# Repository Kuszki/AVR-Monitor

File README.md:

# AVR-Monitor

Zbiór programów i bibliotek oraz projekt urządzenia elektronicznego do badania analogowych sygnałów wolnozmiennych i sterowania urządzeń sygnałami cyfrowymi.

## Programy

### Interfejs

AVR-Interface umożliwia obsługę urządzenia przy pomocy graficznego interfejsu użytkownika. Program pozwala na monitorowanie przebiegów w czasie rzeczywistym i archiwizowanie danych. Ponadto program oferuje możliwość konfiguracji i programowania urządzenia AVR-Monitor.

### Terminal

AVR-Terminal umożliwia komunikacje z urządzeniem AVR-Monitor przy użyciu klasycznego terminalu. Jest to opcja minimalistyczna pozwalająca na zaprogramowanie i konfiguracje urządzenia oraz pozwalająca przetestować większość jego funkcji.

### Biblioteka "Bindings"

AVR-Bindings pozwala na użycie klasy ułatwiającej komunikacje z urządzeniem i nadzoruje jego pracę po podłączeniu.

### Program kontrolera

Stanowi wsad do procesora AVR użytego w projekci układu i płytki PCB.

## Urządzenia

Projekt zawiera urządzenie mikroprocesorowe oparte o mikrokontroler AVR. Na kompletne urządzenie składają się 3 schematy elektryczne - płyty głównej, front-panelu oraz płyty wierzchniej.

## Zależności

- środowisko Qt
- biblioteka KLLibs
- biblioteka QCustomPlot
- biblioteka boost

## Licencja

AVR-Monitor - Zbiór programów i bibliotek oraz projekt urządzenia elektronicznego do badania analogowych sygnałów wolnozmiennych i sterowania urządzeń sygnałami cyfrowymi. Copyright (C) 2015 Łukasz "Kuszki" Dróżdż.

Niniejszy program jest wolnym oprogramowaniem – możesz go rozpowszechniać dalej i/lub modyfikować na warunkach Powszechnej Licencji Publicznej GNU wydanej przez Fundację Wolnego Oprogramowania, według wersji 3 tej Licencji lub dowolnej z późniejszych wersji.

Niniejszy program rozpowszechniany jest z nadzieją, iż będzie on użyteczny – jednak BEZ ŻADNEJ GWARANCJI, nawet domyślnej gwarancji PRZYDATNOŚCI HANDLOWEJ albo PRZYDATNOŚCI DO OKREŚLONYCH ZASTOSOWAŃ. Bliższe informacje na ten temat można uzyskać z Powszechnej Licencji Publicznej GNU.

Kopia Powszechnej Licencji Publicznej GNU powinna zostać ci dostarczona razem z tym programem. Jeżeli nie została dostarczona, odwiedź http://www.gnu.org/licenses/.

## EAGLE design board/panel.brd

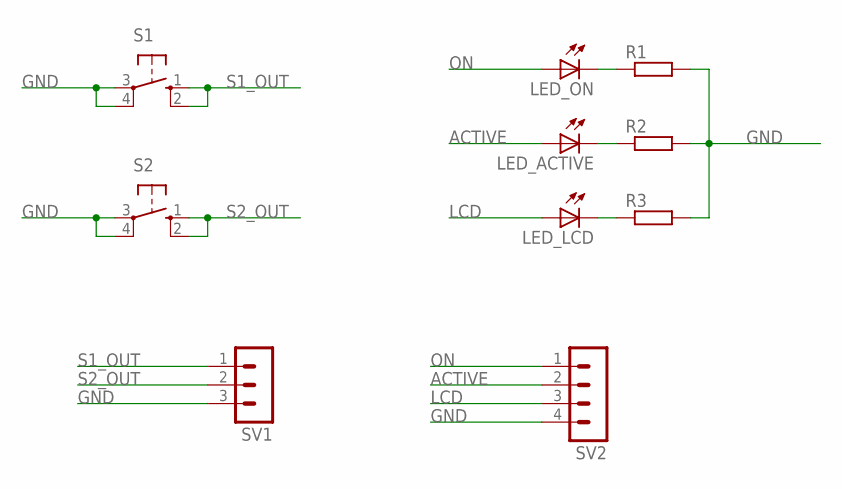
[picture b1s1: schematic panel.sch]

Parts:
LED_ACTIVE: LED_ELD260; LED_LD260
LED_LCD: LED_ELD260; LED_LD260
LED_ON: LED_ELD260; LED_LD260
R1, R2, R3: R-EU_R1206; R1206
S1, S2: 10-XX; B3F-10XX
SV1: MA03-1
SV2: MA04-1

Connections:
ACTIVE: LED_ACTIVE.A, SV2.2
GND: R1.2, R2.2, R3.2, S1.3, S1.4 (P1), S2.3, S2.4 (P1), SV1.3, SV2.4
LCD: LED_LCD.A, SV2.3
unnamed: LED_LCD.K (C), R3.1
unnamed: LED_ACTIVE.K (C), R2.1
unnamed: LED_ON.K (C), R1.1
ON: LED_ON.A, SV2.1
S1_OUT: S1.1 (S), S1.2 (S1), SV1.1
S2_OUT: S2.1 (S), S2.2 (S1), SV1.2

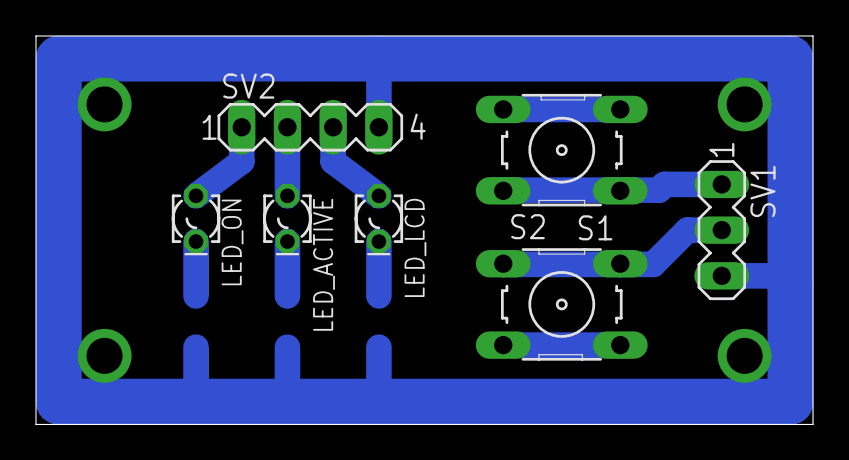
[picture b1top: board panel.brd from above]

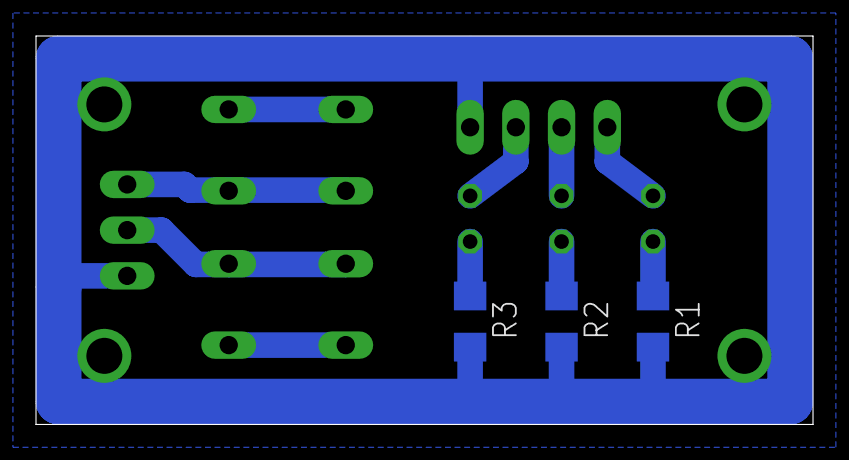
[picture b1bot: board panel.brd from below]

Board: 2 copper layers, 43.2 x 21.6 mm, 10 parts (3 on the bottom side), 9 nets.

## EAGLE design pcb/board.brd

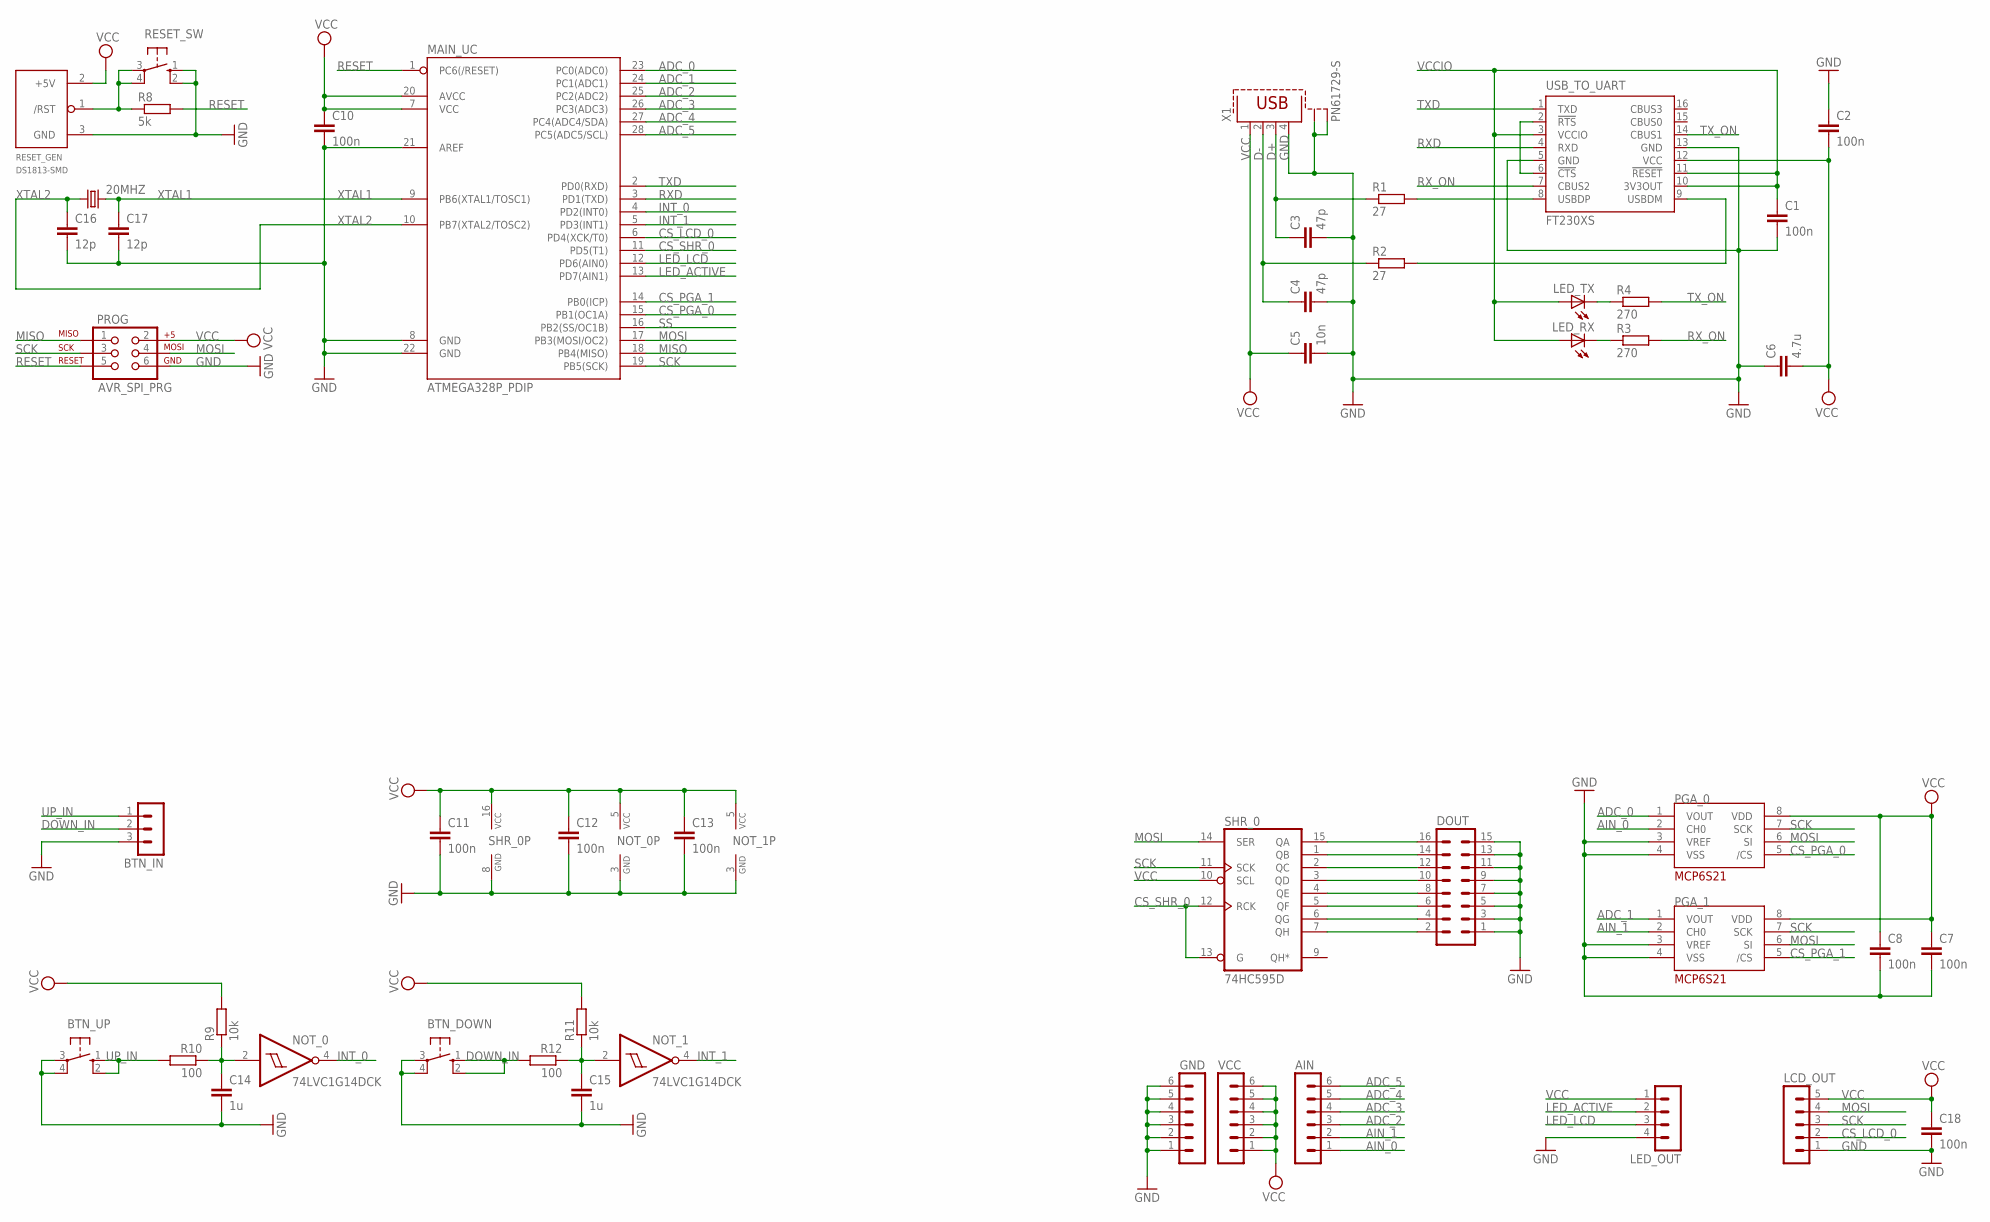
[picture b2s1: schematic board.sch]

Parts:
20MHZ: CRYSTALHC49S; HC49/S
AIN: MA06-1
BTN_DOWN: 10-XX; B3F-10XX
BTN_IN: MA03-1
BTN_UP: 10-XX; B3F-10XX
C1, C2, C7, C8, C10, C11, C12, C13, C18: 100n; C1206
C3, C4: 47p; C1206
C5: 10n; C1206
C6: 4.7u; C025-025X050
C14, C15: 1u; C025-024X044
C16, C17: 12p; C1206
DOUT: MA08-2
GND: MA06-1
LCD_OUT: MA05-1
LED_OUT: MA04-1
LED_RX: LEDLD260; LD260
LED_TX: LEDLD260; LD260
MAIN_UC: ATMEGA328P_PDIP; DIL28-3
NOT_0, NOT_1: 74LVC1G14DCK; SC70-5
PGA_0, PGA_1: MCP6S21I/SN; SO-08
PROG: AVR_SPI_PRG; 2X3
R1, R2: 27; R1206
R3, R4: 270; R1206
R8: 5k; R1206
R9, R11: 10k; R1206
R10, R12: 100; R1206
RESET_GEN: DS1813-SMD; SOT-23
RESET_SW: 10-XX; B3F-10XX
SHR_0: 74HC595D; SO16
USB_TO_UART: FT230XS; SSOP16
VCC: MA06-1
X1: PN61729-S

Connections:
ADC_0: MAIN_UC.23 (PC0(ADC0)), PGA_0.1 (VOUT)
ADC_1: MAIN_UC.24 (PC1(ADC1)), PGA_1.1 (VOUT)
ADC_2: AIN.3, MAIN_UC.25 (PC2(ADC2))
ADC_3: AIN.4, MAIN_UC.26 (PC3(ADC3))
ADC_4: AIN.5, MAIN_UC.27 (PC4(ADC4/SDA))
ADC_5: AIN.6, MAIN_UC.28 (PC5(ADC5/SCL))
AIN_0: AIN.1, PGA_0.2 (CH0)
AIN_1: AIN.2, PGA_1.2 (CH0)
CS_LCD_0: LCD_OUT.2, MAIN_UC.6 (PD4(XCK/T0))
CS_PGA_0: MAIN_UC.15 (PB1(OC1A)), PGA_0.5 (/CS)
CS_PGA_1: MAIN_UC.14 (PB0(ICP)), PGA_1.5 (/CS)
CS_SHR_0: MAIN_UC.11 (PD5(T1)), SHR_0.12 (RCK), SHR_0.13 (G)
D+: C3.1, R1.1, X1.3
D-: C4.1, R2.1, X1.2
DOWN_IN: BTN_DOWN.1 (S), BTN_DOWN.2 (S1), BTN_IN.2, R12.2
INT_0: MAIN_UC.4 (PD2(INT0)), NOT_0.4 (O)
INT_1: MAIN_UC.5 (PD3(INT1)), NOT_1.4 (O)
LED_ACTIVE: LED_OUT.2, MAIN_UC.13 (PD7(AIN1))
LED_LCD: LED_OUT.3, MAIN_UC.12 (PD6(AIN0))
MISO: MAIN_UC.18 (PB4(MISO)), PROG.1
MOSI: LCD_OUT.4, MAIN_UC.17 (PB3(MOSI/OC2)), PGA_0.6 (SI), PGA_1.6 (SI), PROG.4, SHR_0.14 (SER)
unnamed: LED_TX.K (C), R4.1
unnamed: R2.2, USB_TO_UART.9 (USBDM)
unnamed: LED_RX.K (C), R3.1
unnamed: DOUT.16, SHR_0.15 (QA)
unnamed: USB_TO_UART.2 (!RTS), USB_TO_UART.6 (!CTS)
unnamed: R1.2, USB_TO_UART.8 (USBDP)
unnamed: DOUT.14, SHR_0.1 (QB)
unnamed: DOUT.12, SHR_0.2 (QC)
unnamed: DOUT.10, SHR_0.3 (QD)
unnamed: DOUT.8, SHR_0.4 (QE)
unnamed: DOUT.6, SHR_0.5 (QF)
unnamed: DOUT.4, SHR_0.6 (QG)
unnamed: DOUT.2, SHR_0.7 (QH)
unnamed: R8.1, RESET_GEN.1 (/RST), RESET_SW.3, RESET_SW.4 (P1)
unnamed: C14.1, NOT_0.2 (I), R9.1, R10.1
unnamed: C15.1, NOT_1.2 (I), R11.1, R12.1
RESET: MAIN_UC.1 (PC6(/RESET)), PROG.5, R8.2
RXD: MAIN_UC.3 (PD1(TXD)), USB_TO_UART.4 (RXD)
RX_ON: R3.2, USB_TO_UART.7 (CBUS2)
SCK: LCD_OUT.3, MAIN_UC.19 (PB5(SCK)), PGA_0.7 (SCK), PGA_1.7 (SCK), PROG.3, SHR_0.11 (SCK)
SS: MAIN_UC.16 (PB2(SS/OC1B))
TXD: MAIN_UC.2 (PD0(RXD)), USB_TO_UART.1 (TXD)
TX_ON: R4.2, USB_TO_UART.14 (CBUS1)
UP_IN: BTN_IN.1, BTN_UP.1 (S), BTN_UP.2 (S1), R10.2
VCC: C2.2, C5.1, C6.2, C7.1, C8.1, C10.1, C11.1, C12.1, C13.1, C18.1, LCD_OUT.5, LED_OUT.1, MAIN_UC.7 (VCC), MAIN_UC.20 (AVCC), NOT_0.5 (VCC), NOT_1.5 (VCC), PGA_0.8 (VDD), PGA_1.8 (VDD), PROG.2, R9.2, R11.2, RESET_GEN.2 (+5V), SHR_0.10 (SCL), SHR_0.16 (VCC), USB_TO_UART.12 (VCC), VCC.1, VCC.2, VCC.3, VCC.4, VCC.5, VCC.6, X1.1
VCCIO: C1.1, LED_RX.A, LED_TX.A, USB_TO_UART.3 (VCCIO), USB_TO_UART.10 (3V3OUT), USB_TO_UART.11 (!RESET)
XTAL1: 20MHZ.2, C17.1, MAIN_UC.9 (PB6(XTAL1/TOSC1))
XTAL2: 20MHZ.1, C16.1, MAIN_UC.10 (PB7(XTAL2/TOSC2))

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
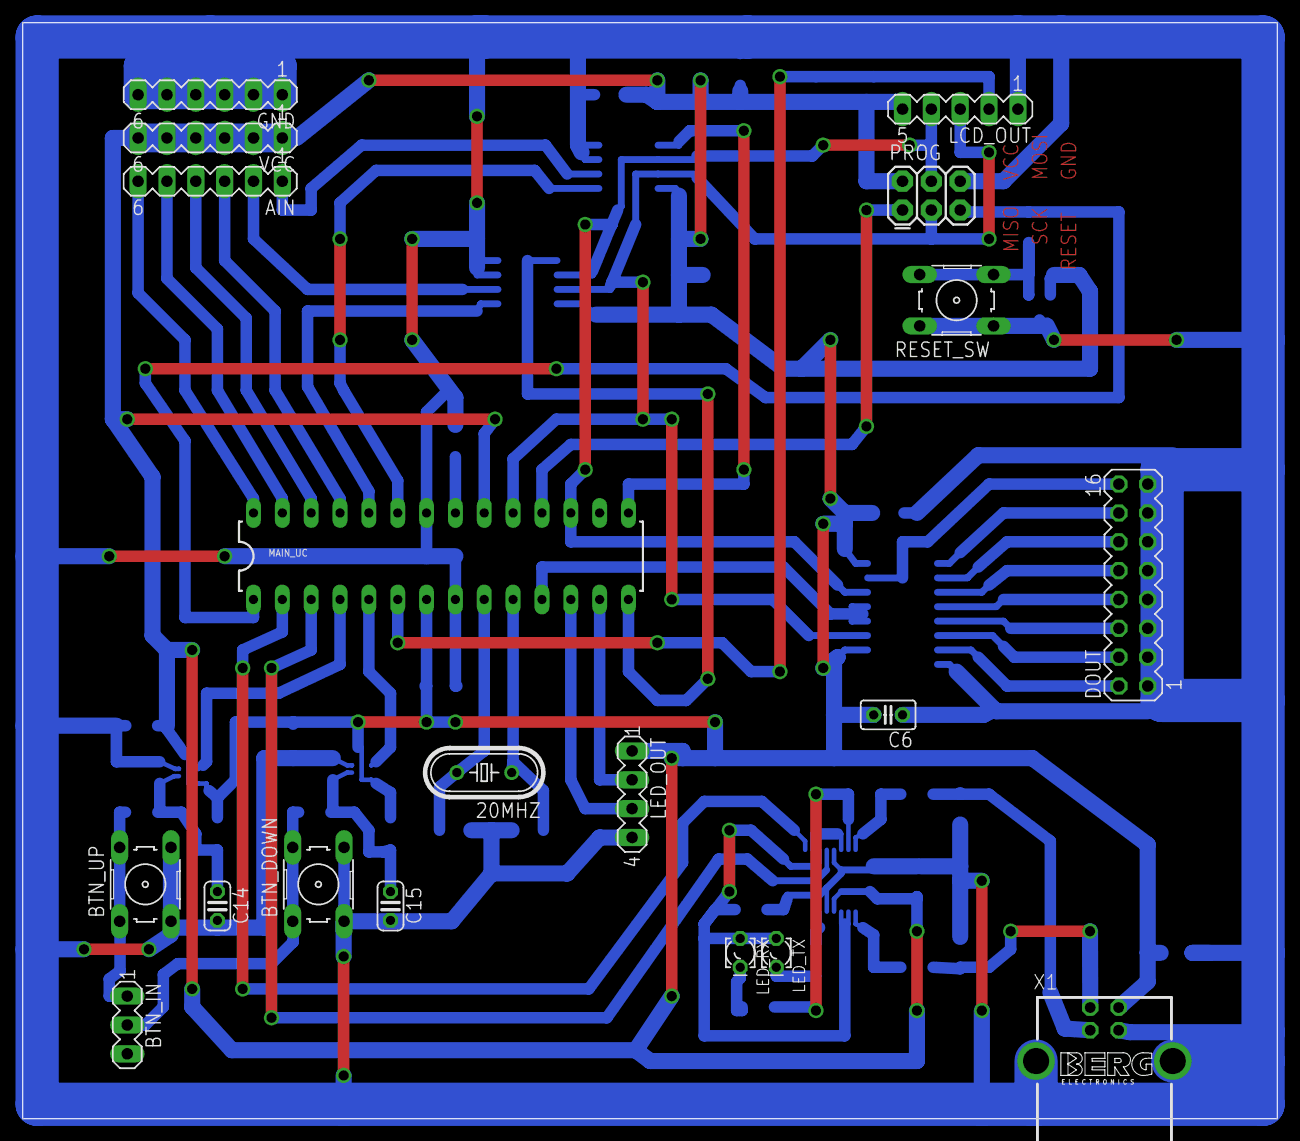
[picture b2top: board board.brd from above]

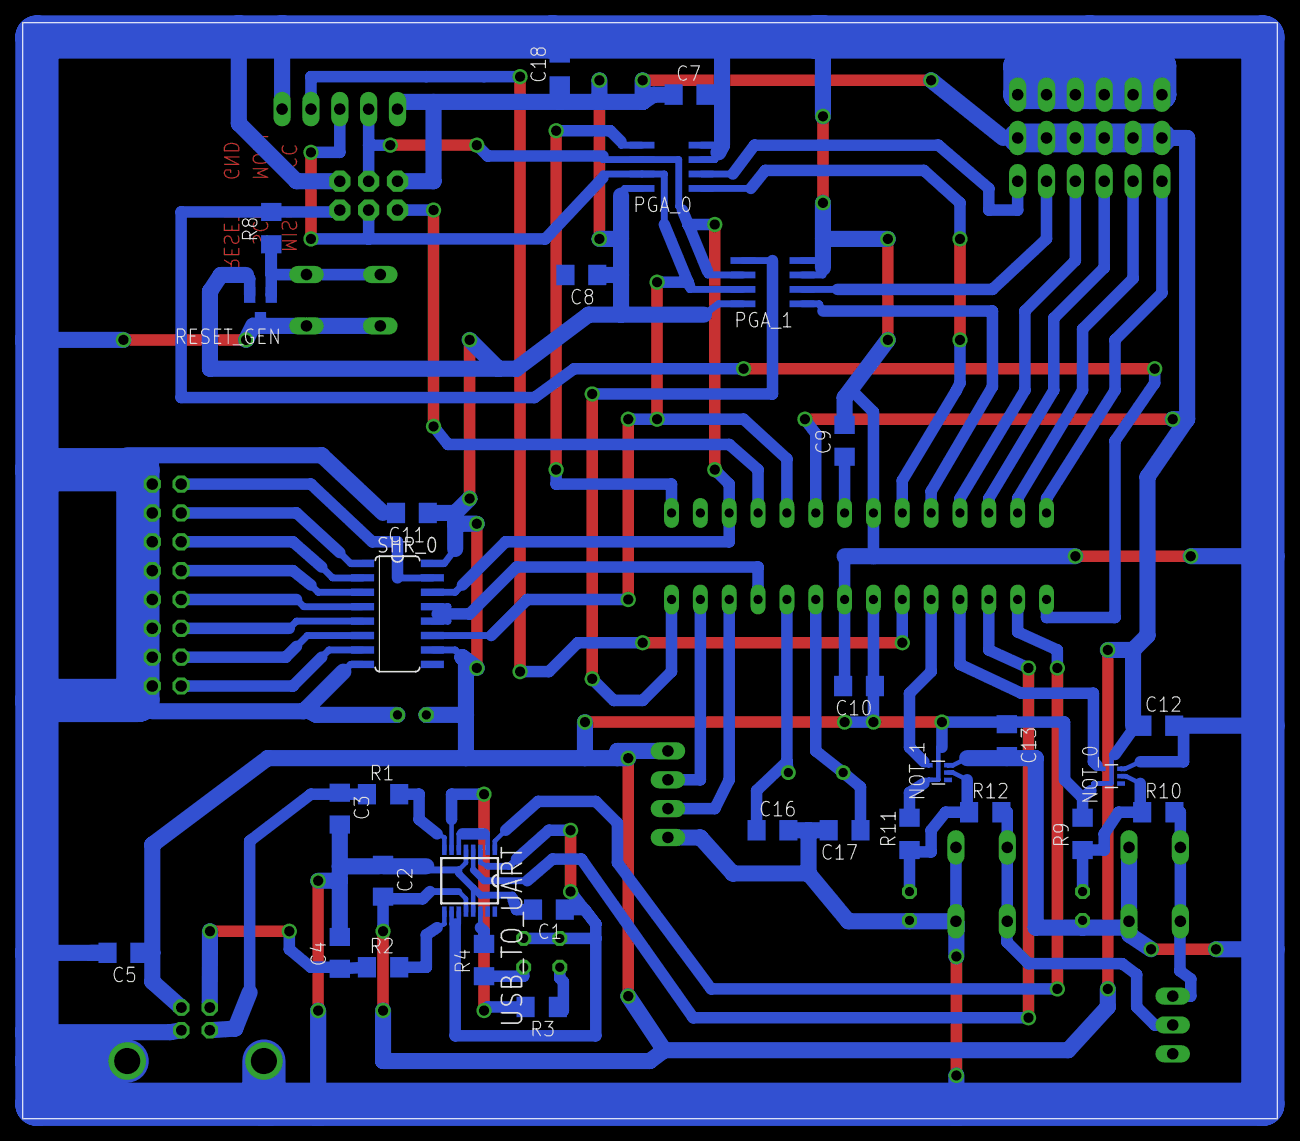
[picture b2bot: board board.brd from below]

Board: 2 copper layers, 110.5 x 96.5 mm, 50 parts (31 on the bottom side), 50 nets.

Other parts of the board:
C9: 10n; C1206

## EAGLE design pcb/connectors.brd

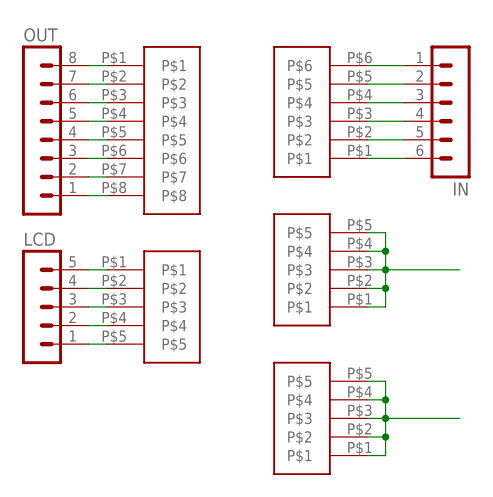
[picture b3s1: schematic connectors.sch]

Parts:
IN: MA06-1
LCD: MA05-1
OUT: MA08-1
U$1: KOSTKA_2.5MM_X8; X8
U$2, U$4, U$6: KOSTKA_2.5MM_X5; X5
U$3: KOSTKA_2.5MM_X6; X6

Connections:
GND: U$4.P$1, U$4.P$2, U$4.P$3, U$4.P$4, U$4.P$5
unnamed: OUT.8, U$1.P$1
unnamed: OUT.7, U$1.P$2
unnamed: OUT.6, U$1.P$3
unnamed: OUT.5, U$1.P$4
unnamed: OUT.4, U$1.P$5
unnamed: OUT.3, U$1.P$6
unnamed: OUT.2, U$1.P$7
unnamed: OUT.1, U$1.P$8
unnamed: LCD.1, U$6.P$5
unnamed: IN.1, U$3.P$6
unnamed: IN.2, U$3.P$5
unnamed: IN.3, U$3.P$4
unnamed: IN.4, U$3.P$3
unnamed: IN.5, U$3.P$2
unnamed: IN.6, U$3.P$1
unnamed: LCD.2, U$6.P$4
unnamed: LCD.3, U$6.P$3
unnamed: LCD.4, U$6.P$2
unnamed: LCD.5, U$6.P$1
VCC: U$2.P$1, U$2.P$2, U$2.P$3, U$2.P$4, U$2.P$5

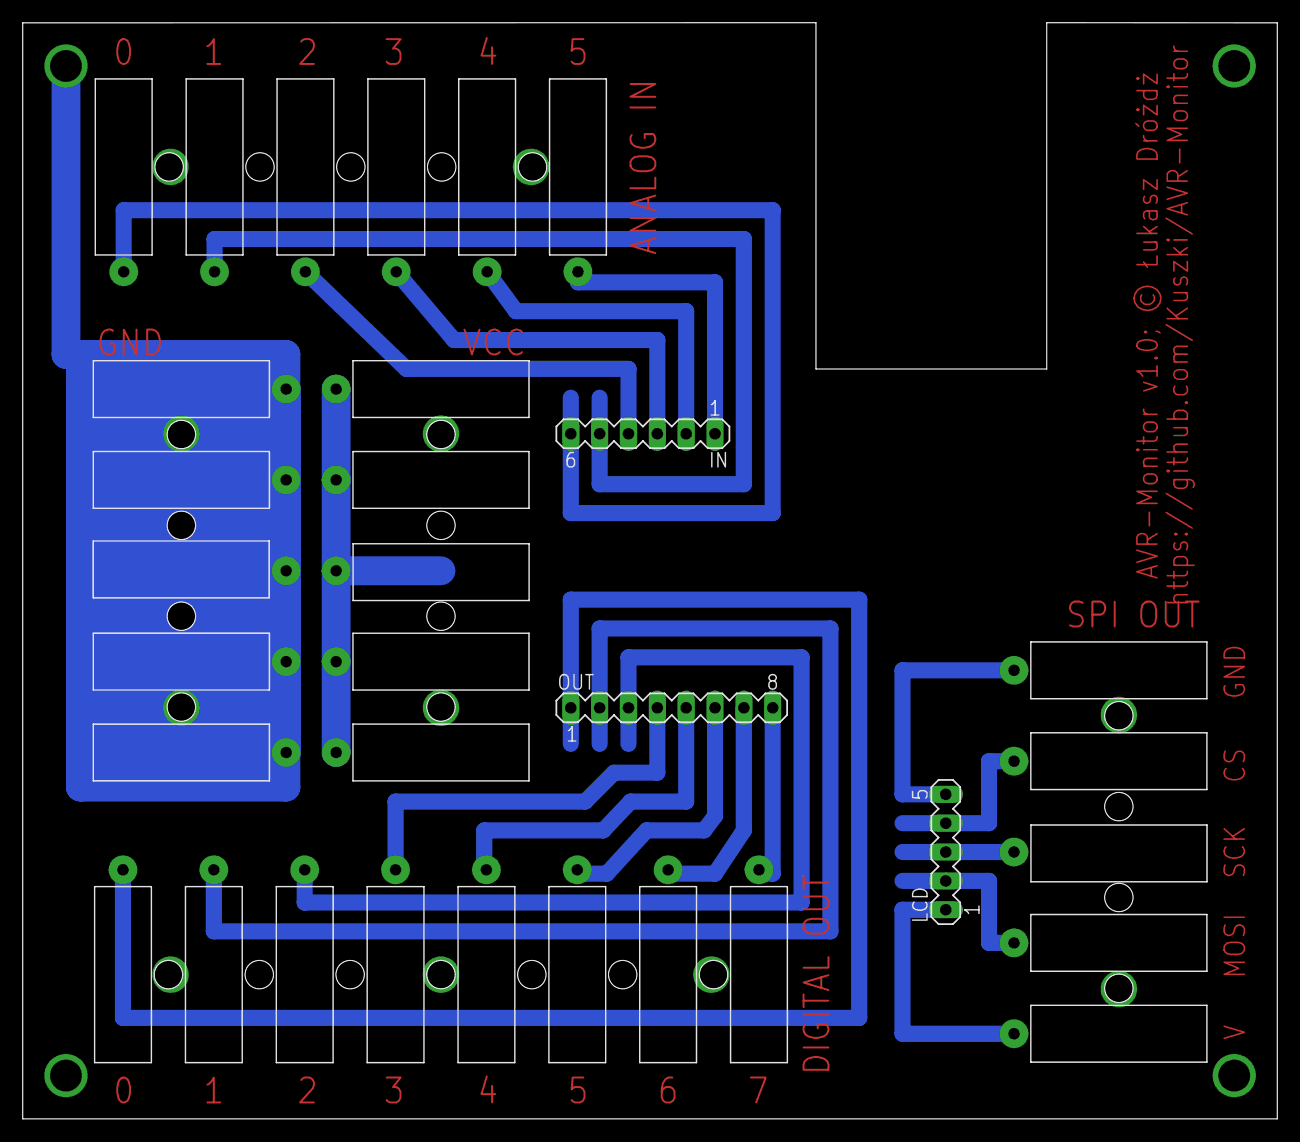
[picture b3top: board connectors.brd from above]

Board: 2 copper layers, 110.5 x 96.5 mm, 8 parts (0 on the bottom side), 21 nets.

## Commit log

2015-07-07 Add new files
2015-07-07 Upgrade board
2015-07-10 Add complete PCB
2015-07-10 Update license to GNU GPL v3
2015-07-26 Final version of PCB
2015-07-27 Update gitignore
2015-07-27 Correct PCB
2015-07-27 Add UC program source
2015-07-28 Implement UC program
2015-07-28 Reorganize project
2015-07-31 Great upgrade and reorganization
2015-08-01 Implement watchdog and many features - all is stable
2015-08-01 Add dosc + fix some issues. Everything stable
2015-08-04 Implement some part of interface
2015-08-04 Change tab pos
2015-08-05 Implement next interface parts
2015-08-05 Next part of changes
2015-08-09 Next part of updates
2015-09-05 Add tool buttons text
2015-09-05 Datale "pro.user"
2015-09-09 Add new forms
2015-09-10 Add new widgets. Prapare to implement ploting
2015-09-10 Add icons
2015-09-12 Implement plot features [SID]
2015-09-13 Implement ploting features
2015-09-13 Convert paths to relative
2015-09-13 Add license desc
2015-09-13 Add translations
2015-09-13 Update translations
2015-09-13 Minor update
2015-09-14 Add some new dialogs
2015-09-14 Minor updates
2015-09-15 Translator updates
2015-09-16 Add average tool
2015-09-16 Interface updates
2015-09-16 Minor changes
2015-09-16 Try to test OpenGL
2015-09-16 Next try with openGL
2015-09-16 Revert OpenGL experiments
2015-09-18 Fix sensor delete
2015-09-20 Update controler code
2015-09-20 Move log into terminal widget
2015-09-20 Update e-mail adress
2015-09-20 Update database check
2015-09-20 Update tab order
2015-09-20 Change slot name
2015-09-20 Update interface layout
2015-09-20 Add blocks limit to log window
2015-09-20 Upgrade shift state switch
2015-09-20 Fixed double gain set
2015-09-21 Implement "fail" function in case of controler fail
2015-09-21 Implement on fail measurements stop
2015-09-21 Add ReadMe
2015-09-25 Some fixes
2015-09-25 Some optimizations
2015-09-25 Prepare to implement SQL server support for web interface
2015-09-26 Implement HTTP view client
2015-09-27 Some minor fixes
2015-09-27 Add termination handler and fix signal handling when killed
2015-09-27 Add terminal app translations
2015-09-28 Change floating numbers precision
2015-09-28 Change -O3 to -Os
2015-09-28 Improve some code
2015-09-28 Make `work as master` possible
2015-09-29 Fix master/slave colisions
2015-09-29 Update web slite
2015-09-29 Improve POSIX-like signal handling in terminal application
2015-09-29 Minor changes in signal handlers
2015-09-30 Change QSettings engine
2015-10-02 Update dependences
2015-10-02 Change `get` behavior with params. Need test
2015-10-03 Change layout
2015-10-03 Fix axis delete crash
2015-10-03 Fix axis delete database issues
2015-10-03 Fix many device frezes
2015-10-03 Change baud rate to 115200 bps
2015-10-04 Improve script features
2015-10-26 Fix default output issue and make int and det style sensors work
2015-10-27 Improve some features
2015-11-09 Update interface
2015-11-21 Add new features for future use
2015-12-04 Update Bridge to work with new KLLibs version
2015-12-04 Update Controller to work with new KLLibs version
2015-12-04 Update Interface to work with new KLLibs version
2015-12-04 Fix function memory leak
2015-12-04 Update docs
2015-12-05 Resize About dialog
2015-12-06 Minor doc fix
2015-12-08 Synchronize Script thread with env changes
2015-12-09 Update controller build
2015-12-15 Update build
2015-12-16 Fix data leaks when changing plot visibility
2015-12-16 Enable C++14 features
2015-12-17 Fix build on old Qt versions
2016-01-16 Update master to slave switch - improve stability
2016-01-16 Fixed issue with changing work status
2016-01-17 Fix "put" binding
2016-06-21 Add new feature - sliders
2016-06-23 Rewrite app core items and database management
2016-06-23 Fix many crashes
2016-06-23 Next part of fixes
2016-06-23 Minor UI fixes
2016-06-23 Update headers
2016-06-23 Remove central widget
2016-06-23 Hide helper on startup
2016-06-24 UI update
2016-06-25 Rebuild controller program
2016-06-25 Interface update
2016-07-05 Update validator
2016-07-23 Set slider pageStep to 1
2016-08-08 Fix threat unsafe lambda call
2016-08-08 Incrase frequency
2016-08-10 Cleanup libs
2016-08-11 Some interface features improve
2016-08-11 Improve plot export
2016-08-13 Implement PWM output handling
2016-08-14 Update version
2016-08-14 Small translation update
2016-08-15 Update device info string
2016-08-15 Update strings
2016-08-15 Add single value output into shift register
2016-08-15 Redesign error codes
2016-08-15 Format only
2016-08-15 Fix watchdog reset
2016-08-15 Implement device fail watcher
2016-08-19 Update comments
2016-08-19 Implement evaluation time measurement
2016-08-19 Remove system variables from script variables
2016-08-20 Remove timer due high performance looses
2016-08-20 Improve script check - fix wrong script generation
2016-08-20 Revert testing lines
2016-08-20 Fix master code generation
2016-10-29 Update code to KLLibs new version
2016-10-29 Implement moving average interface
2016-10-29 Implement moving average feature
2016-10-29 Add moving average translations
2016-10-29 Change moving average samples limit
2016-10-29 Reimplement moving average feature
2016-11-02 Fix minor bug
2016-11-11 Implement moving average weights options
2016-11-12 Correct tab order
2016-11-12 Update name validator
2016-11-15 Update program size due KLLibs update
2016-11-24 Implement import/export env
2016-11-24 Fix some visual problems
2016-11-24 Implement rest of import/export env
2016-11-24 Implement "dt" variable [doesn't fully work with device as master]
2016-11-24 Fix weights calculation after changing list into vector
2016-11-24 Improve filtering
2016-11-24 Some interface improvements
2016-11-25 Lock multiple variable refresh on script evaluation
2016-11-25 Change container to Qt5 compability
2016-11-26 Correct translation
2016-11-26 Implement better error handling [TEST]
2016-11-26 Correct error handling
2016-11-26 Remove unsafe lambda connections
2016-11-26 Next part of unsafe lambda fixes
2016-11-26 Remove testing debug output
2016-11-26 Update translations [TESTING]
2016-11-27 Secure error message from infinite spam
2016-11-27 All bindings without error returns NAN
2016-11-27 Limit maximum plot size
2016-11-27 Some cleanup
2016-11-27 Resize dialog width
2016-12-13 Update program info due KLLibs update
2017-01-30 Add null strings check
2017-02-01 Minor UI changes
2017-02-02 Update UI
2017-02-02 Add icons to widgets
2017-02-12 Update build info
2017-02-19 Remove QDebug
2017-03-11 Add path to save/open env
2017-03-12 Build update
2017-03-12 Update build due KLLibs update
2017-03-19 Some interface updates
2017-03-19 Remove unused check
2017-03-19 Add 'unsigned' to char params
2017-03-20 Add 'Override' flag to force setting same values
2017-03-25 Remove debug include
2017-03-25 Fix plot restart issue
2017-05-05 Update info header
2017-05-06 Change samplint time decimals
2022-09-19 Fix icon

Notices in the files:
parts and their libraries:
SparkFun-DigitalIC: Licensing: Creative Commons ShareAlike 4.0 International - https://creativecommons.org/licenses/by-sa/4.0
